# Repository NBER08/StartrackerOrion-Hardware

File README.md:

<h1 align="center">Orion Main</h1>

<p align="center" width="100%">
  
</p>

***

<p align="center">
  
&nbsp; &nbsp; &nbsp; &nbsp;
  
</p>

***

## SPECIFICATIONS

| Parameter | Value | 
| --- | --- |
| Dimensions | 86.06 × 71.93 mm |

***

## DIRECTORY STRUCTURE

    .
    ├─ Computations       # Misc calculations
    ├─ HTML               # HTML files for generated webpage
    ├─ Images             # Pictures and renders
    │
    ├─ kibot_resources    # External resources for KiBot
    │  ├─ colors          # Color theme for KiCad
    │  ├─ fonts           # Fonts used in the project
    │  ├─ scripts         # External scripts used with KiBot
    │  └─ templates       # Templates for KiBot generated reports
    │
    ├─ kibot_yaml         # KiBot YAML config files
    ├─ KiRI               # KiRI (PCB diff viewer) files
    │
    ├─ lib                # KiCad footprint and symbol libraries
    │  ├─ 3d_models       # Component 3D models
    │  ├─ lib_fp          # Footprint libraries
    │  └─ lib_sym         # Symbol libraries
    │
    ├─ Logos              # Logos
    │
    ├─ Manufacturing      # Assembly and fabrication documents
    │  ├─ Assembly        # Assembly documents (BoM, pos, notes)
    │  │
    │  └─ Fabrication     # Fabrication documents (ZIP, notes)
    │     ├─ Drill Tables # CSV drill tables
    │     └─ Gerbers      # Gerbers
    │
    ├─ Report             # Reports for ERC/DRC
    ├─ Schematic          # PDF of schematic
    ├─ Templates          # Title block templates
    ├─ Testing
    │  └─ Testpoints      # Testpoints tables      
    │
    └─ Variants           # Outputs for assembly variants

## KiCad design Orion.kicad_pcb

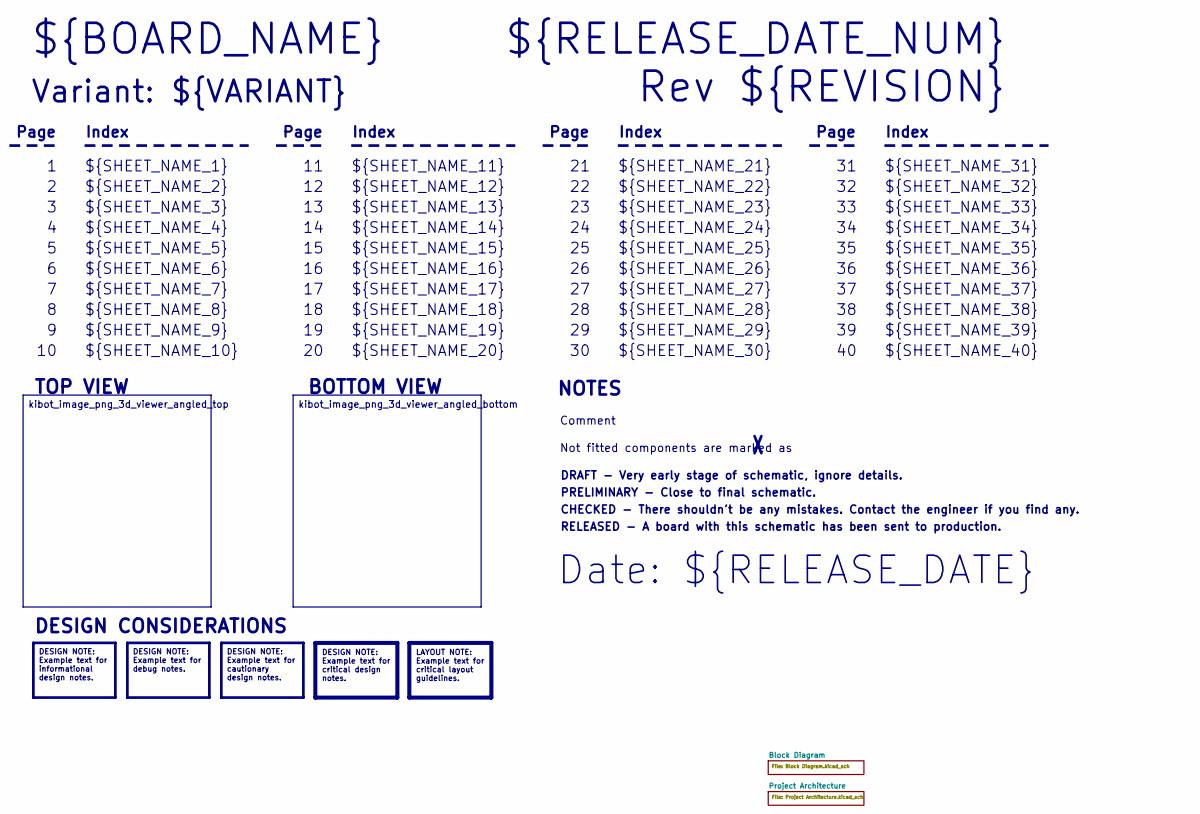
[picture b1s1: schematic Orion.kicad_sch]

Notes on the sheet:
Variant: ${VARIANT}
RELEASED - A board with this schematic has been sent to production.
${SHEET_NAME_24}
Index
Page
PRELIMINARY - Close to final schematic.
${SHEET_NAME_22}
DRAFT - Very early stage of schematic, ignore details.
${SHEET_NAME_12}
${SHEET_NAME_8}
${SHEET_NAME_2}
${SHEET_NAME_5}
${SHEET_NAME_20}
${SHEET_NAME_23}
${RELEASE_DATE_NUM}
${SHEET_NAME_35}
Not fitted components are marked as
${SHEET_NAME_11}
${SHEET_NAME_6}
${SHEET_NAME_37}
${SHEET_NAME_26}
${SHEET_NAME_36}
Rev ${REVISION}
${SHEET_NAME_15}
CHECKED - There shouldn't be any mistakes. Contact the engineer if you find any.
BOTTOM VIEW
${SHEET_NAME_14}
${SHEET_NAME_21}
${SHEET_NAME_17}
${SHEET_NAME_18}
Date: ${RELEASE_DATE}
${SHEET_NAME_7}
${SHEET_NAME_31}
${BOARD_NAME}
NOTES
${SHEET_NAME_40}
${SHEET_NAME_39}
${SHEET_NAME_32}
${SHEET_NAME_1}
${SHEET_NAME_9}

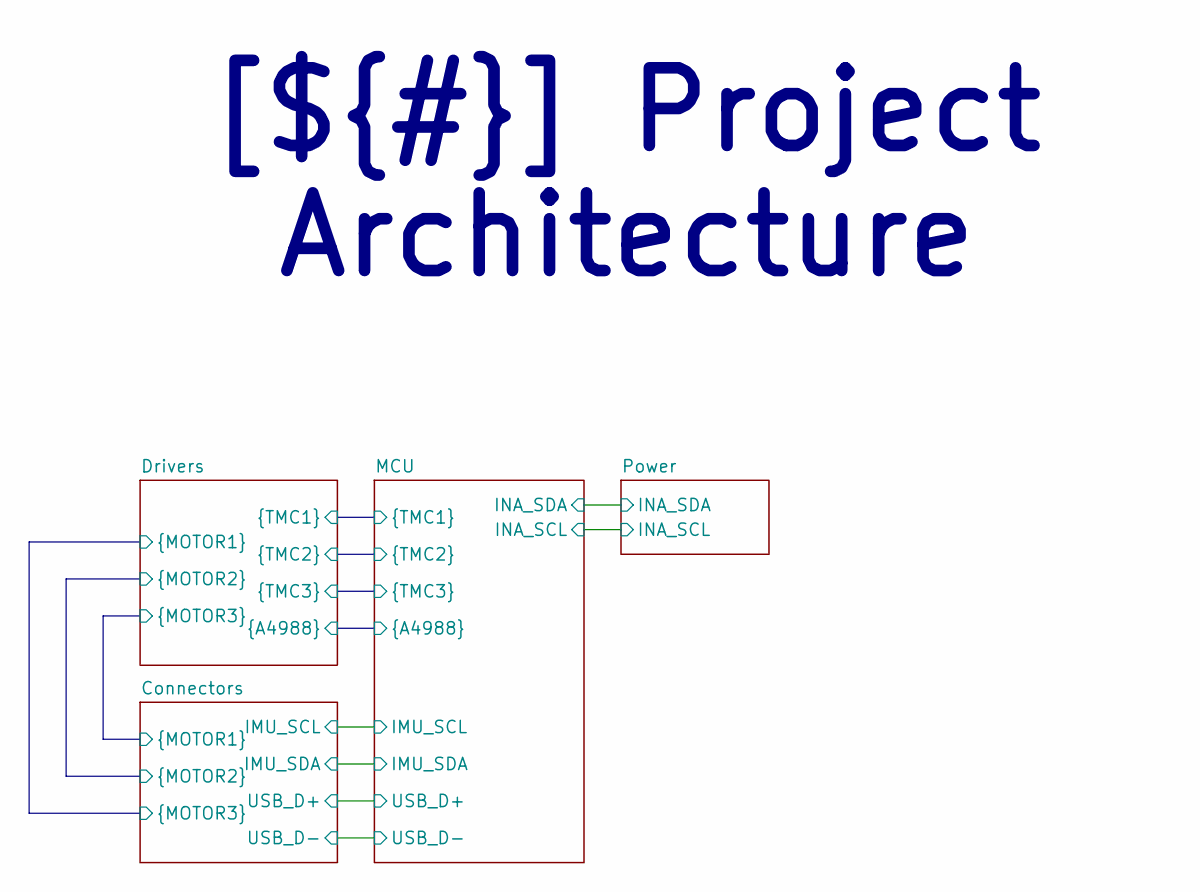
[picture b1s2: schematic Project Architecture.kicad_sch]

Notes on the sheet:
[${#}] ${TITLE}

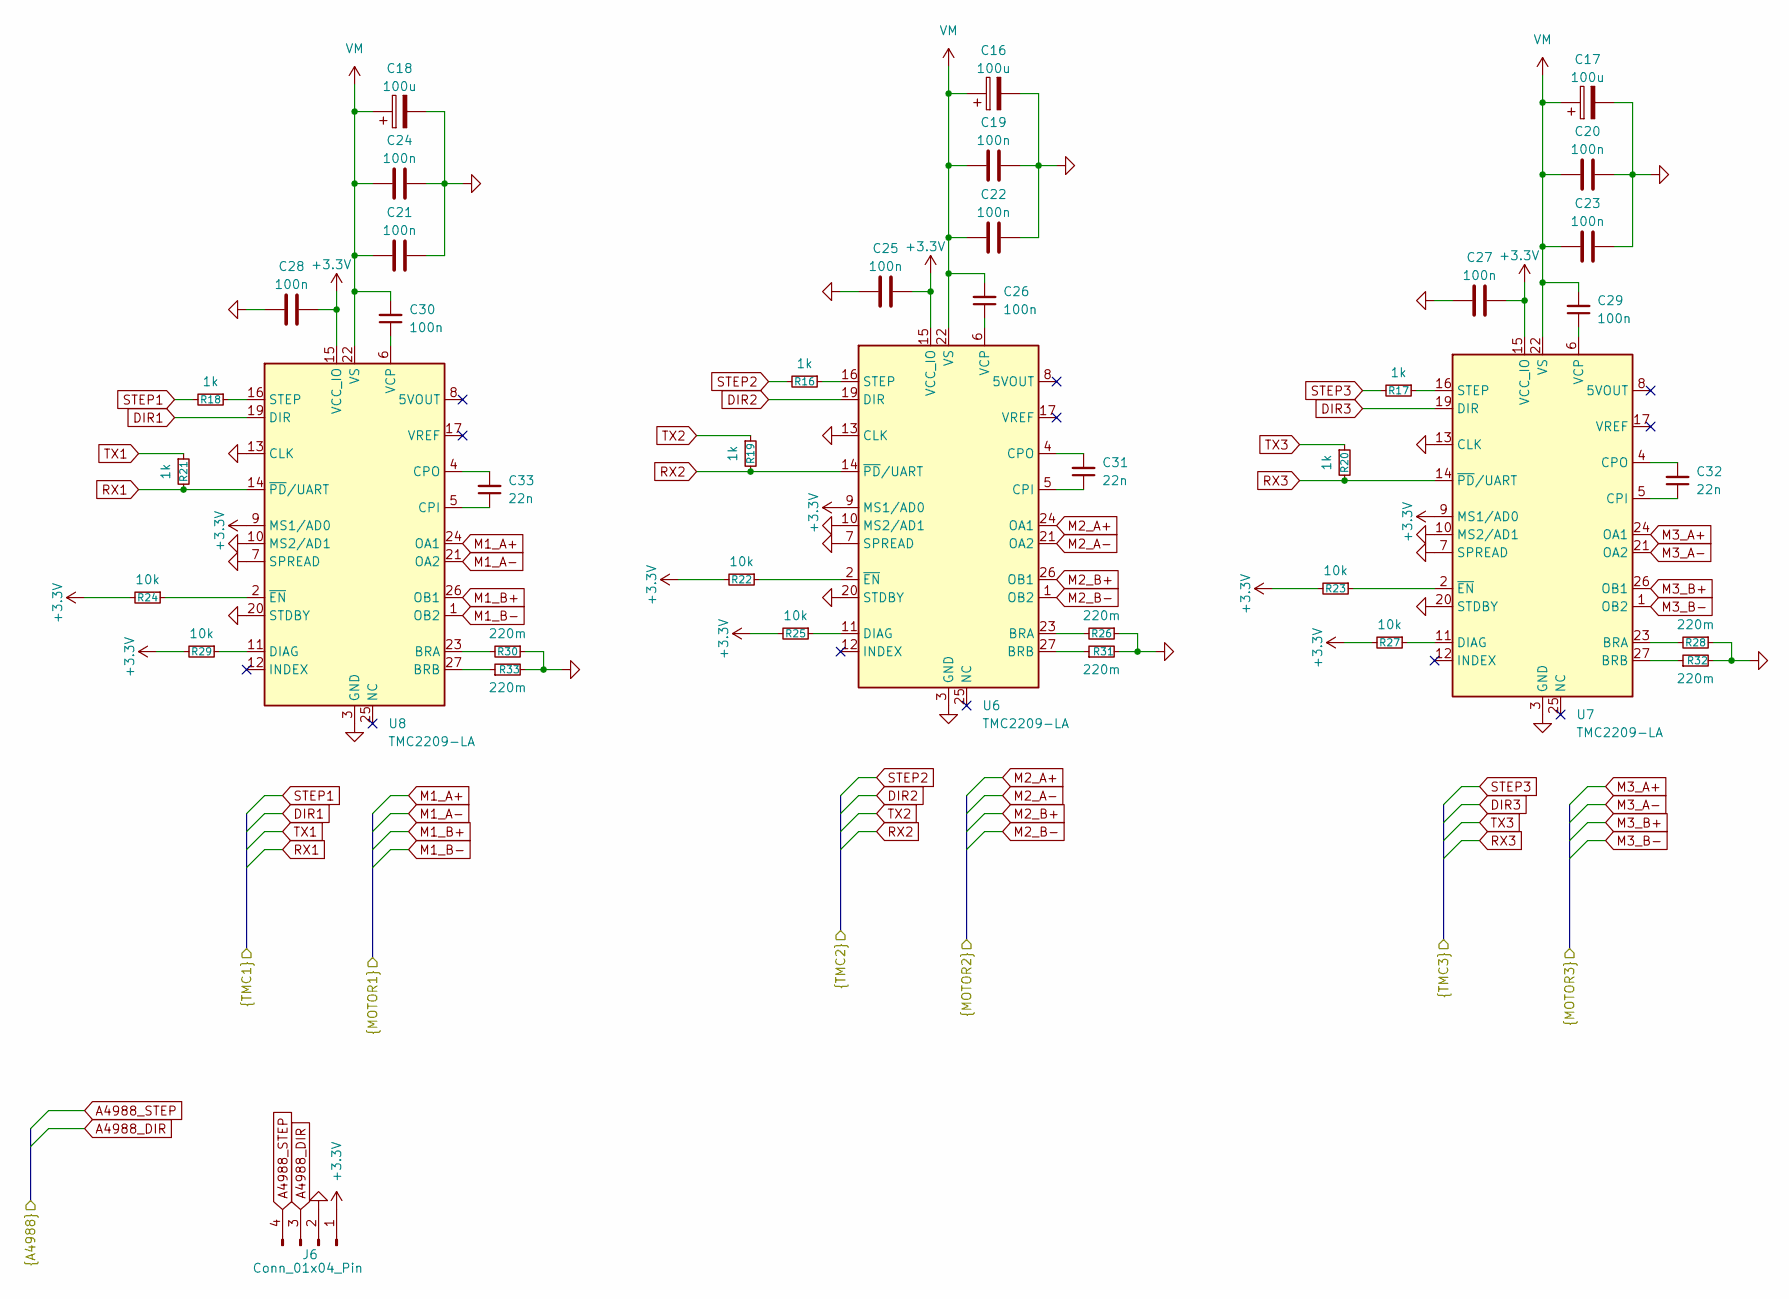
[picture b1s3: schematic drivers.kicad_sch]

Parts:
C16, C17, C18: 100u; CP_Radial_D5.0mm_P2.00mm
C19, C20, C21, C22, C23, C24, C25, C26, C27, C28, C29, C30: 100n; C_0603_1608Metric_Pad1.08x0.95mm_HandSolder
C31, C32, C33: 22n; C_0603_1608Metric_Pad1.08x0.95mm_HandSolder
J6: Conn_01x04_Pin; PinHeader_1x04_P2.54mm_Vertical
R16, R17, R18, R19, R20, R21: 1k; R_0603_1608Metric_Pad0.98x0.95mm_HandSolder
R22, R23, R24, R25, R27, R29: 10k; R_0603_1608Metric_Pad0.98x0.95mm_HandSolder
R26, R28, R30, R31, R32, R33: 220m; R_2512_6332Metric_Pad1.40x3.35mm_HandSolder
U6, U7, U8: TMC2209-LA; VQFN-28-1EP_5x5mm_P0.5mm_EP3.7x3.7mm

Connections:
+3.3V: C25.2, C27.2, C28.2, J6.1, R22.2, R23.2, R24.2, R25.2, R27.2, R29.2, U6.9 (MS1/AD0), U6.15 (VCC_IO), U7.9 (MS1/AD0), U7.15 (VCC_IO), U8.9 (MS1/AD0), U8.15 (VCC_IO); also elsewhere on the board
A4988_DIR: J6.3; also elsewhere on the board
A4988_STEP: J6.4; also elsewhere on the board
DIR1: U8.19 (DIR); also elsewhere on the board
DIR2: U6.19 (DIR); also elsewhere on the board
DIR3: U7.19 (DIR); also elsewhere on the board
GND: C16.2, C17.2, C18.2, C19.2, C20.2, C21.2, C22.2, C23.2, C24.2, C25.1, C27.1, C28.1, J6.2, R26.1, R28.1, R30.1, R31.2, R32.2, R33.2, U6.3 (GND), U6.7 (SPREAD), U6.10 (MS2/AD1), U6.13 (CLK), U6.18 (GND), U6.20 (STDBY), U6.29 (GND), U7.3 (GND), U7.7 (SPREAD), U7.10 (MS2/AD1), U7.13 (CLK), U7.18 (GND), U7.20 (STDBY), U7.29 (GND), U8.3 (GND), U8.7 (SPREAD), U8.10 (MS2/AD1), U8.13 (CLK), U8.18 (GND), U8.20 (STDBY), U8.29 (GND); also elsewhere on the board
M1_A+: U8.24 (OA1); also elsewhere on the board
M1_A-: U8.21 (OA2); also elsewhere on the board
M1_B+: U8.26 (OB1); also elsewhere on the board
M1_B-: U8.1 (OB2); also elsewhere on the board
M2_A+: U6.24 (OA1); also elsewhere on the board
M2_A-: U6.21 (OA2); also elsewhere on the board
M2_B+: U6.26 (OB1); also elsewhere on the board
M2_B-: U6.1 (OB2); also elsewhere on the board
M3_A+: U7.24 (OA1); also elsewhere on the board
M3_A-: U7.21 (OA2); also elsewhere on the board
M3_B+: U7.26 (OB1); also elsewhere on the board
M3_B-: U7.1 (OB2); also elsewhere on the board
unnamed: R26.2, U6.23 (BRA)
unnamed: R31.1, U6.27 (BRB)
unnamed: C31.1, U6.5 (CPI)
unnamed: C31.2, U6.4 (CPO)
unnamed: R25.1, U6.11 (DIAG)
unnamed: R16.1, U6.16 (STEP)
unnamed: C26.1, U6.6 (VCP)
unnamed: R22.1, U6.2 (~EN)
unnamed: R28.2, U7.23 (BRA)
unnamed: R32.1, U7.27 (BRB)
unnamed: C32.1, U7.5 (CPI)
unnamed: C32.2, U7.4 (CPO)
unnamed: R27.1, U7.11 (DIAG)
unnamed: R17.1, U7.16 (STEP)
unnamed: C29.1, U7.6 (VCP)
unnamed: R23.1, U7.2 (~EN)
unnamed: R30.2, U8.23 (BRA)
unnamed: R33.1, U8.27 (BRB)
unnamed: C33.1, U8.5 (CPI)
unnamed: C33.2, U8.4 (CPO)
unnamed: R29.1, U8.11 (DIAG)
unnamed: R18.1, U8.16 (STEP)
unnamed: C30.1, U8.6 (VCP)
unnamed: R24.1, U8.2 (~EN)
RX1: R21.2, U8.14 (~PD/UART); also elsewhere on the board
RX2: R19.2, U6.14 (~PD/UART); also elsewhere on the board
RX3: R20.2, U7.14 (~PD/UART); also elsewhere on the board
STEP1: R18.2; also elsewhere on the board
STEP2: R16.2; also elsewhere on the board
STEP3: R17.2; also elsewhere on the board
TX1: R21.1; also elsewhere on the board
TX2: R19.1; also elsewhere on the board
TX3: R20.1; also elsewhere on the board
VM: C16.1, C17.1, C18.1, C19.1, C20.1, C21.1, C22.1, C23.1, C24.1, C26.2, C29.2, C30.2, U6.22 (VS), U6.28 (VS), U7.22 (VS), U7.28 (VS), U8.22 (VS), U8.28 (VS); also elsewhere on the board

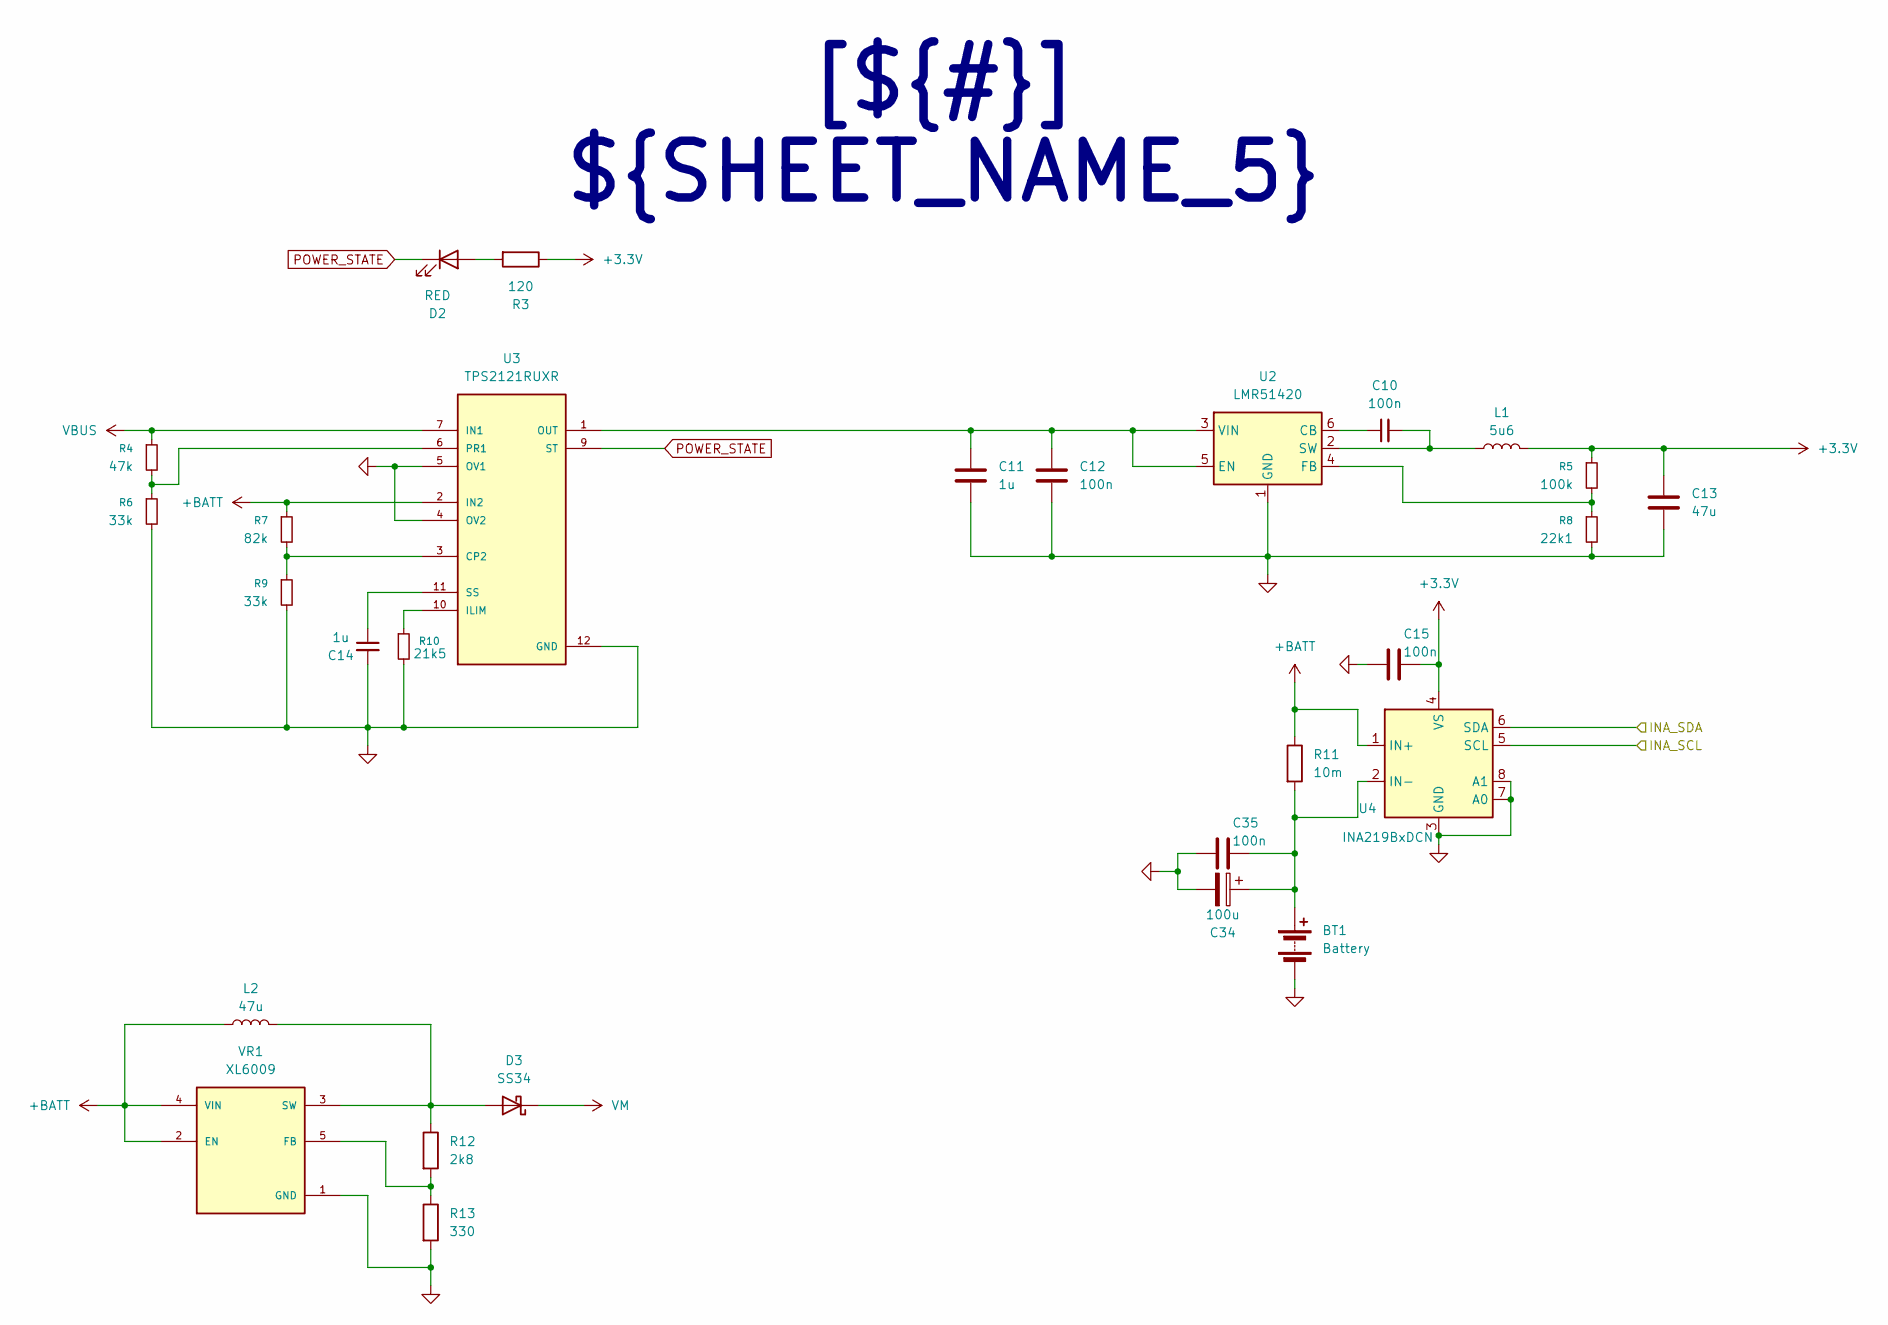
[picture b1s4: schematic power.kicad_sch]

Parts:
BT1: Battery; JST_XH_B2B-XH-A_1x02_P2.50mm_Vertical
C10, C12, C15, C35: 100n; C_0603_1608Metric_Pad1.08x0.95mm_HandSolder
C11, C14: 1u; C_0603_1608Metric_Pad1.08x0.95mm_HandSolder
C13: 47u; C_0603_1608Metric_Pad1.08x0.95mm_HandSolder
C34: 100u; CP_Radial_D5.0mm_P2.00mm
D2: RED; LED_0603_1608Metric_Pad1.05x0.95mm_HandSolder
D3: SS34; D_SMA_Handsoldering
L1: 5u6; WE-XHMI_4040
L2: 47u; L_Changjiang_FXL1365
R3: 120; R_0603_1608Metric_Pad0.98x0.95mm_HandSolder
R4: 47k; R_0603_1608Metric_Pad0.98x0.95mm_HandSolder
R5: 100k; R_0603_1608Metric_Pad0.98x0.95mm_HandSolder
R6, R9: 33k; R_0603_1608Metric_Pad0.98x0.95mm_HandSolder
R7: 82k; R_0603_1608Metric_Pad0.98x0.95mm_HandSolder
R8: 22k1; R_0603_1608Metric_Pad0.98x0.95mm_HandSolder
R10: 21k5; R_0603_1608Metric_Pad0.98x0.95mm_HandSolder
R11: 10m; R_0805_2012Metric_Pad1.20x1.40mm_HandSolder
R12: 2k8; R_0603_1608Metric_Pad0.98x0.95mm_HandSolder
R13: 330; R_0603_1608Metric_Pad0.98x0.95mm_HandSolder
U2: LMR51420; SOT-23-6_Handsoldering
U3: TPS2121RUXR; IC_TPS2121RUXR
U4: INA219BxDCN; SOT-23-8
VR1: XL6009; DPAK170P1435X465-6N; PARTREV 1.1

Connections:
+3.3V: C13.1, C15.2, L1.2, R3.1, R5.1, U4.4 (VS); also elsewhere on the board
+BATT: L2.1, R7.1, R11.1, U3.2 (IN2), U3.2_1 (IN2), U4.1 (IN+), VR1.2 (EN), VR1.4 (VIN); also elsewhere on the board
/Project Architecture/MCU/INA_SCL: U4.5 (SCL); also elsewhere on the board
/Project Architecture/MCU/INA_SDA: U4.6 (SDA); also elsewhere on the board
GND: BT1.2 (-), C11.2, C12.2, C13.2, C14.2, C15.1, C34.2, C35.1, R6.2, R8.2, R9.2, R10.2, R13.2, U2.1 (GND), U3.4 (OV2), U3.5 (OV1), U3.12 (GND), U4.3 (GND), U4.7 (A0), U4.8 (A1), VR1.1 (GND); also elsewhere on the board
unnamed: BT1.1 (+), C34.1, C35.2, R11.2, U4.2 (IN-)
unnamed: D2.2 (A), R3.2
unnamed: D3.2 (A), L2.2, R12.1, VR1.3 (SW), VR1.6 (SW)
unnamed: C10.1, U2.6 (CB)
unnamed: C11.1, C12.1, U2.3 (VIN), U2.5 (EN), U3.1 (OUT), U3.1_1 (OUT), U3.8 (OUT), U3.8_1 (OUT)
unnamed: R5.2, R8.1, U2.4 (FB)
unnamed: C10.2, L1.1, U2.2 (SW)
unnamed: R7.2, R9.1, U3.3 (CP2)
unnamed: R10.1, U3.10 (ILIM)
unnamed: R4.2, R6.1, U3.6 (PR1)
unnamed: C14.1, U3.11 (SS)
unnamed: R12.2, R13.1, VR1.5 (FB)
POWER_STATE: D2.1 (K), U3.9 (ST)
VBUS: R4.1, U3.7 (IN1), U3.7_1 (IN1); also elsewhere on the board
VM: D3.1 (K); also elsewhere on the board

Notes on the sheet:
[${#}] ${SHEET_NAME_5}

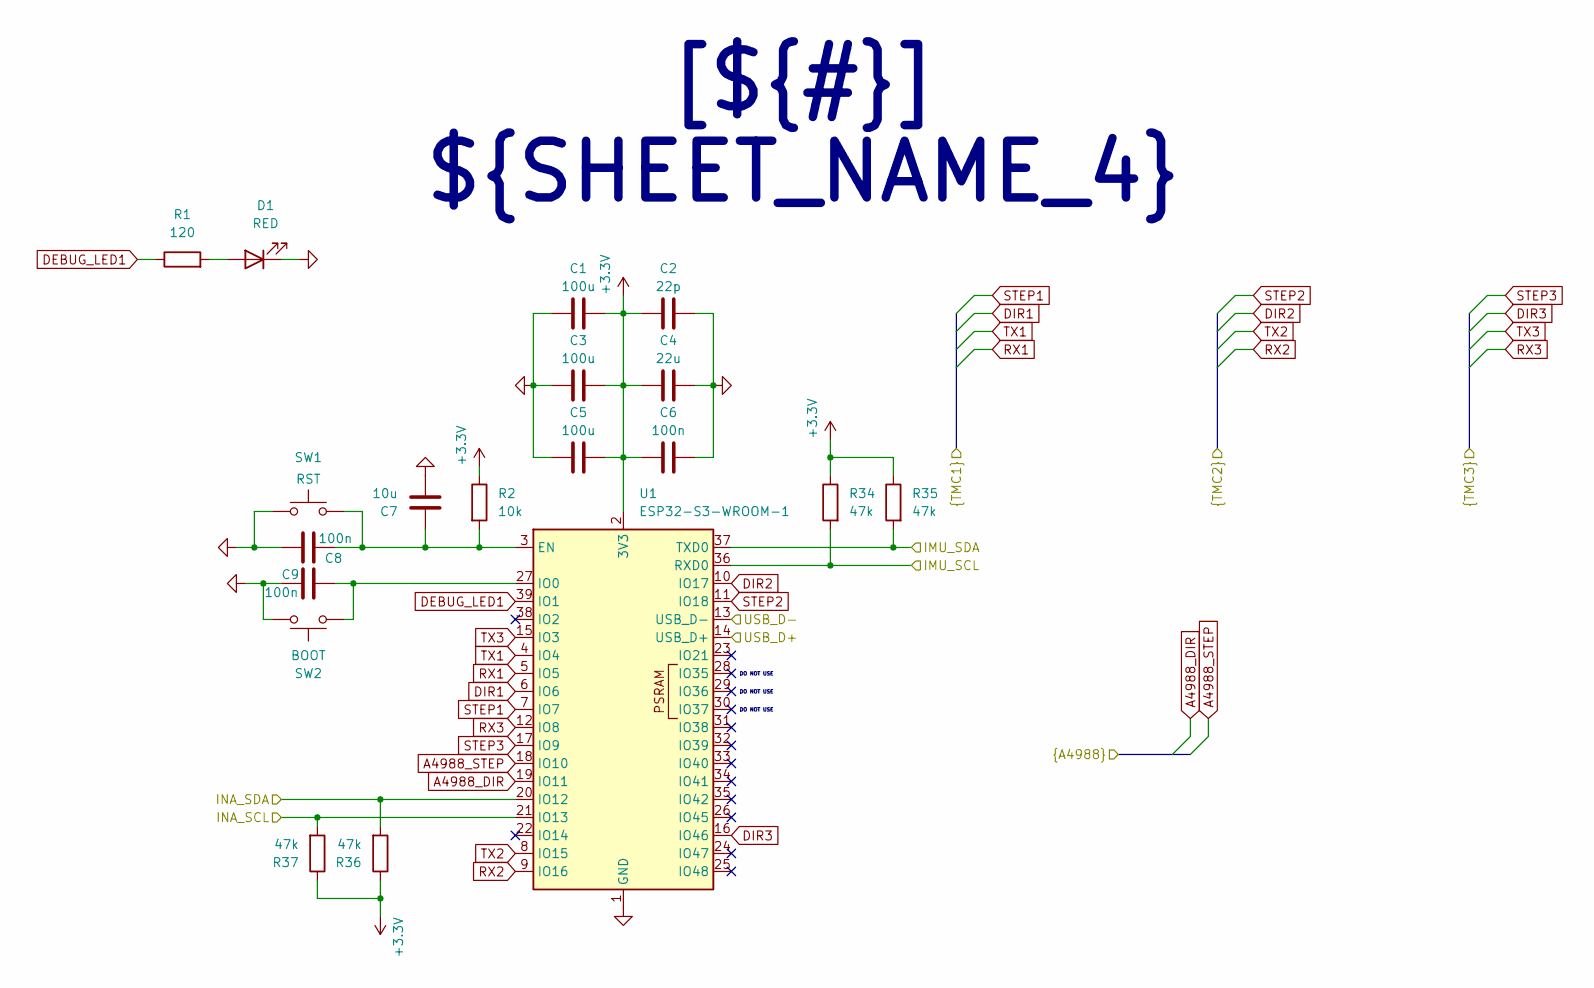
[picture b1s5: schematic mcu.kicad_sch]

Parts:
C1, C3, C5: 100u; C_1206_3216Metric_Pad1.33x1.80mm_HandSolder
C2: 22p; C_0603_1608Metric_Pad1.08x0.95mm_HandSolder
C4: 22u; C_0603_1608Metric_Pad1.08x0.95mm_HandSolder
C6, C8, C9: 100n; C_0603_1608Metric_Pad1.08x0.95mm_HandSolder
C7: 10u; C_0603_1608Metric_Pad1.08x0.95mm_HandSolder
D1: RED; LED_0603_1608Metric_Pad1.05x0.95mm_HandSolder
R1: 120; R_0603_1608Metric_Pad0.98x0.95mm_HandSolder
R2: 10k; R_0603_1608Metric_Pad0.98x0.95mm_HandSolder
R34, R35, R36, R37: 47k; R_0603_1608Metric_Pad0.98x0.95mm_HandSolder
SW1: RST; SW_SPST_PTS647_Sx38
SW2: BOOT; SW_SPST_PTS647_Sx38
U1: ESP32-S3-WROOM-1; ESP32-S3-WROOM-1_novias

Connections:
+3.3V: C1.2, C2.1, C3.2, C4.1, C5.2, C6.1, R2.1, R34.1, R35.1, R36.1, R37.1, U1.2 (3V3); also elsewhere on the board
/Project Architecture/Connectors/IMU_SCL: R34.2, U1.36 (RXD0); also elsewhere on the board
/Project Architecture/Connectors/IMU_SDA: R35.2, U1.37 (TXD0); also elsewhere on the board
/Project Architecture/Connectors/USB_D+: U1.14 (USB_D+); also elsewhere on the board
/Project Architecture/Connectors/USB_D-: U1.13 (USB_D-); also elsewhere on the board
/Project Architecture/MCU/INA_SCL: R37.2, U1.21 (IO13); also elsewhere on the board
/Project Architecture/MCU/INA_SDA: R36.2, U1.20 (IO12); also elsewhere on the board
A4988_DIR: U1.19 (IO11); also elsewhere on the board
A4988_STEP: U1.18 (IO10); also elsewhere on the board
DEBUG_LED1: R1.1, U1.39 (IO1)
DIR1: U1.6 (IO6); also elsewhere on the board
DIR2: U1.10 (IO17); also elsewhere on the board
DIR3: U1.16 (IO46); also elsewhere on the board
GND: C1.1, C2.2, C3.1, C4.2, C5.1, C6.2, C7.2, C8.1, C9.1, D1.1 (K), SW1.1, SW2.1, U1.1 (GND), U1.40 (GND), U1.41 (GND); also elsewhere on the board
unnamed: D1.2 (A), R1.2
unnamed: C7.1, C8.2, R2.2, SW1.2, U1.3 (EN)
unnamed: C9.2, SW2.2, U1.27 (IO0)
RX1: U1.5 (IO5); also elsewhere on the board
RX2: U1.9 (IO16); also elsewhere on the board
RX3: U1.12 (IO8); also elsewhere on the board
STEP1: U1.7 (IO7); also elsewhere on the board
STEP2: U1.11 (IO18); also elsewhere on the board
STEP3: U1.17 (IO9); also elsewhere on the board
TX1: U1.4 (IO4); also elsewhere on the board
TX2: U1.8 (IO15); also elsewhere on the board
TX3: U1.15 (IO3); also elsewhere on the board

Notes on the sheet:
DO NOT USE
[${#}] ${SHEET_NAME_4}

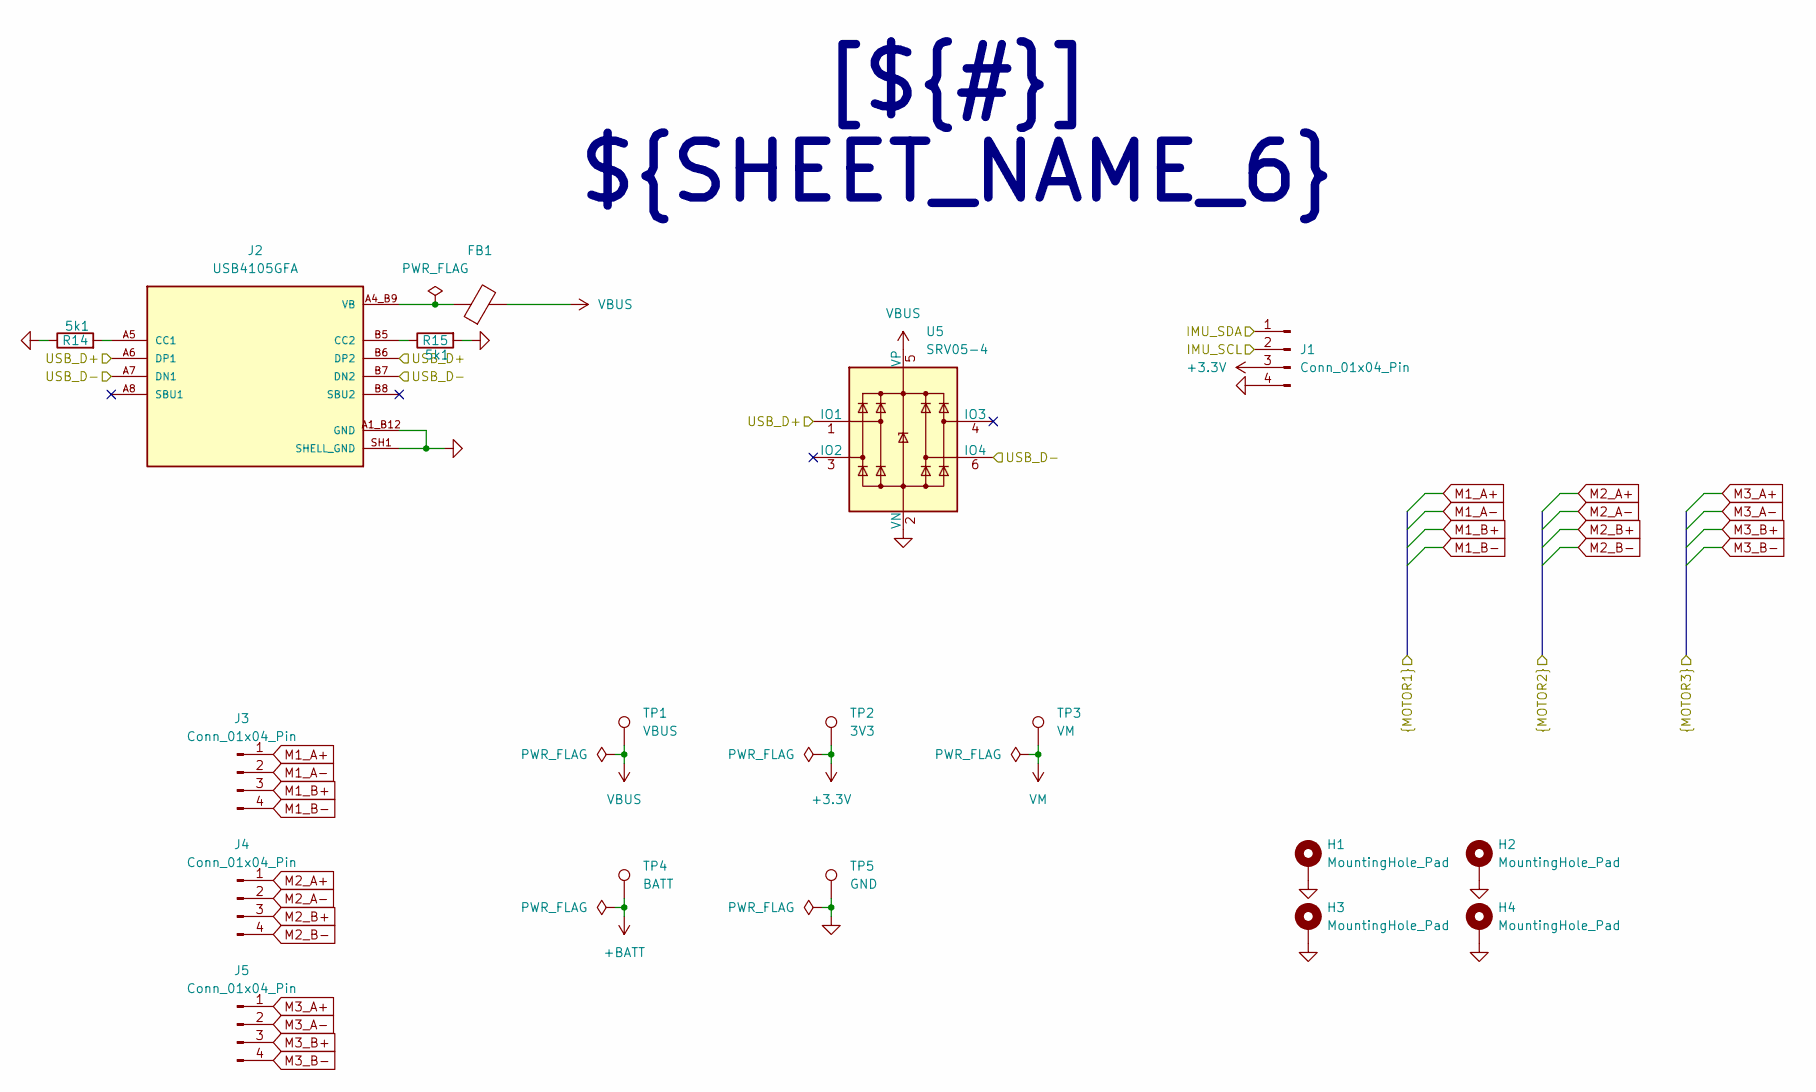
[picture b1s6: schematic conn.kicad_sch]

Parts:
FB1: LI0603G121R-10; L_0603_1608Metric_Pad1.05x0.95mm_HandSolder
H1, H2, H3, H4: MountingHole_Pad; MountingHole_3.2mm_M3_DIN965_Pad
J1: Conn_01x04_Pin; PinHeader_1x04_P2.54mm_Vertical
J2: USB4105GFA; GCT_USB4105GFA; PARTREV B3
J3, J4, J5: Conn_01x04_Pin; JST_XH_B4B-XH-A_1x04_P2.50mm_Vertical
R14, R15: 5k1; R_0603_1608Metric_Pad0.98x0.95mm_HandSolder
TP1: VBUS; TestPoint_Pad_D1.5mm
TP2: 3V3; TestPoint_Pad_D1.5mm
TP3: VM; TestPoint_Pad_D1.5mm
TP4: BATT; TestPoint_Pad_D1.5mm
TP5: GND; TestPoint_Pad_D1.5mm
U5: SRV05-4; SOT-23-6_Handsoldering

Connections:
+3.3V: J1.3, TP2.1 (1_1); also elsewhere on the board
+BATT: TP4.1 (1_1); also elsewhere on the board
/Project Architecture/Connectors/IMU_SCL: J1.2; also elsewhere on the board
/Project Architecture/Connectors/IMU_SDA: J1.1; also elsewhere on the board
/Project Architecture/Connectors/USB_D+: J2.A6 (DP1), J2.B6 (DP2), U5.1 (IO1); also elsewhere on the board
/Project Architecture/Connectors/USB_D-: J2.A7 (DN1), J2.B7 (DN2), U5.6 (IO4); also elsewhere on the board
GND: H1.1 (1_1), H2.1 (1_1), H3.1 (1_1), H4.1 (1_1), J1.4, J2.A1_B12 (GND), J2.B1_A12 (GND), J2.SH1 (SHELL_GND), J2.SH2 (SHELL_GND), J2.SH3 (SHELL_GND), J2.SH4 (SHELL_GND), R14.1, R15.2, TP5.1 (1_1), U5.2 (VN); also elsewhere on the board
M1_A+: J3.1; also elsewhere on the board
M1_A-: J3.2; also elsewhere on the board
M1_B+: J3.3; also elsewhere on the board
M1_B-: J3.4; also elsewhere on the board
M2_A+: J4.1; also elsewhere on the board
M2_A-: J4.2; also elsewhere on the board
M2_B+: J4.3; also elsewhere on the board
M2_B-: J4.4; also elsewhere on the board
M3_A+: J5.1; also elsewhere on the board
M3_A-: J5.2; also elsewhere on the board
M3_B+: J5.3; also elsewhere on the board
M3_B-: J5.4; also elsewhere on the board
unnamed: J2.A5 (CC1), R14.2
unnamed: J2.B5 (CC2), R15.1
VB: FB1.1, J2.A4_B9 (VB), J2.B4_A9 (VB)
VBUS: FB1.2, TP1.1 (1_1), U5.5 (VP); also elsewhere on the board
VM: TP3.1 (1_1); also elsewhere on the board

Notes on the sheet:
[${#}] ${SHEET_NAME_6}

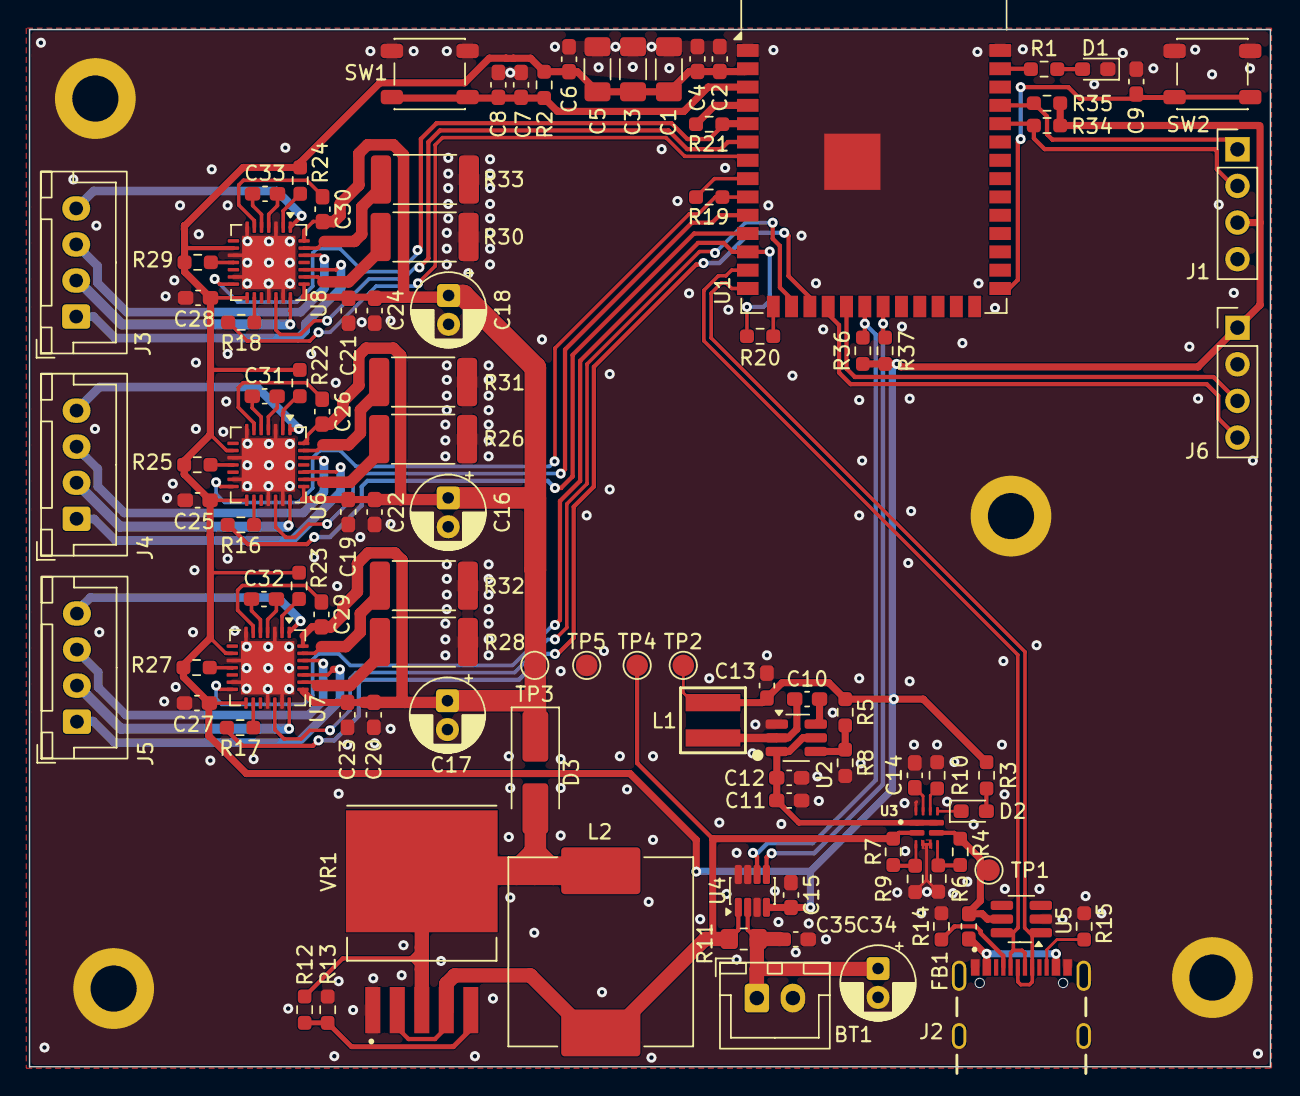
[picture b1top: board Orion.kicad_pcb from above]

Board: 2 copper layers, 86.1 x 71.9 mm, 105 parts (0 on the bottom side), 81 nets.

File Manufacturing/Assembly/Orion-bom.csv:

Row,Quantity Per PCB,References,Value,Datasheet,Footprint,Description,Manufacturer,Manufacturer Part Number,Supplier Part Number
1,1,BT1,Battery,,JST_XH_B2B-XH-A_1x02_P2.50mm_Vertical,Multiple-cell battery,,,
2,1,C2,22p,,C_0603_1608Metric_Pad1.08x0.95mm_HandSolder,Unpolarized capacitor,,,
3,3,C31 C32 C33,22n,,C_0603_1608Metric_Pad1.08x0.95mm_HandSolder,50V,,,
4,19,C6 C8 C9 C10 C12 C15 C19 C20 C21 C22 C23 C24 C25 C26 C27 C28 C29 C30 C35,100n,,C_0603_1608Metric_Pad1.08x0.95mm_HandSolder,"Unpolarized capacitor Unpolarized capacitor, small symbol 16V",,,
5,2,C11 C14,1u,,C_0603_1608Metric_Pad1.08x0.95mm_HandSolder,"Unpolarized capacitor Unpolarized capacitor, small symbol",,,
6,1,C7,10u,,C_0603_1608Metric_Pad1.08x0.95mm_HandSolder,Unpolarized capacitor,,,
7,1,C4,22u,,C_0603_1608Metric_Pad1.08x0.95mm_HandSolder,Unpolarized capacitor,,,
8,2,C13 L2,47u,,C_0603_1608Metric_Pad1.08x0.95mm_HandSolder,Unpolarized capacitor Inductor,,,
9,7,C1 C3 C5 C16 C17 C18 C34,100u,,C_1206_3216Metric_Pad1.33x1.80mm_HandSolder,Unpolarized capacitor low ESR,,,
10,2,D1 D2,RED,,LED_0603_1608Metric_Pad1.05x0.95mm_HandSolder,Light emitting diode,,,
11,1,D3,SS34,https://www.vishay.com/docs/88751/ss32.pdf,D_SMA_Handsoldering,"40V 3A Schottky Diode, SMA",,,
12,1,FB1,LI0603G121R-10,,L_0603_1608Metric_Pad1.05x0.95mm_HandSolder,Ferrite bead,,,
13,5,J1 J3 J4 J5 J6,Conn_01x04_Pin,,PinHeader_1x04_P2.54mm_Vertical,"Generic connector, single row, 01x04, script generated",,,
14,1,J2,USB4105GFA,,GCT_USB4105GFA,"USB-C (USB TYPE-C) USB 2.0 Receptacle Connector 24 (16+8 Dummy) Position Surface Mount, Right Angle; Through Hole",Global Connector Technology,,
15,1,L1,5u6,,WE-XHMI_4040,Inductor,,,
16,1,R11,10m,,R_0805_2012Metric_Pad1.20x1.40mm_HandSolder,Resistor,,,
17,6,R26 R28 R30 R31 R32 R33,220m,,R_2512_6332Metric_Pad1.40x3.35mm_HandSolder,"Resistor, small symbol",,,
18,2,R1 R3,120,,R_0603_1608Metric_Pad0.98x0.95mm_HandSolder,Resistor,,,
19,1,R13,330,,R_0603_1608Metric_Pad0.98x0.95mm_HandSolder,Resistor,,,
20,6,R16 R17 R18 R19 R20 R21,1k,,R_0603_1608Metric_Pad0.98x0.95mm_HandSolder,"Resistor, small symbol",,,
21,1,R12,2k8,,R_0603_1608Metric_Pad0.98x0.95mm_HandSolder,Resistor,,,
22,2,R14 R15,5k1,,R_0603_1608Metric_Pad0.98x0.95mm_HandSolder,Resistor,,,
23,7,R2 R22 R23 R24 R25 R27 R29,10k,,R_0603_1608Metric_Pad0.98x0.95mm_HandSolder,"Resistor Resistor, small symbol",,,
24,1,R10,21k5,,R_0603_1608Metric_Pad0.98x0.95mm_HandSolder,"Resistor, small symbol",,,
25,1,R8,22k1,,R_0603_1608Metric_Pad0.98x0.95mm_HandSolder,"Resistor, small symbol",,,
26,2,R6 R9,33k,,R_0603_1608Metric_Pad0.98x0.95mm_HandSolder,"Resistor, small symbol",,,
27,5,R4 R34 R35 R36 R37,47k,,R_0603_1608Metric_Pad0.98x0.95mm_HandSolder,"Resistor, small symbol",,,
28,1,R7,82k,,R_0603_1608Metric_Pad0.98x0.95mm_HandSolder,"Resistor, small symbol",,,
29,1,R5,100k,,R_0603_1608Metric_Pad0.98x0.95mm_HandSolder,"Resistor, small symbol",,,
30,1,SW2,BOOT,,SW_SPST_PTS647_Sx38,"Push button switch, generic, two pins",,,
31,1,SW1,RST,,SW_SPST_PTS647_Sx38,"Push button switch, generic, two pins",,,
32,1,U1,ESP32-S3-WROOM-1,https://www.espressif.com/sites/default/files/documentation/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,ESP32-S3-WROOM-1_novias,"RF Module, ESP32-S3 SoC, Wi-Fi 802.11b/g/n, Bluetooth, BLE, 32-bit, 3.3V, onboard antenna, SMD",,,
33,1,U4,INA219BxDCN,http://www.ti.com/lit/ds/symlink/ina219.pdf,SOT-23-8,"Zero-Drift, HighAccuracy, Bidirectional Current/Power Monitor (0-26V) With I2C Interface, SOT-23-8",,,
34,1,U2,LMR51420,https://www.ti.com/lit/ds/symlink/lmr51430.pdf,SOT-23-6_Handsoldering,"4.5-V to 36-V, 3-A synchronous buck converter with 40-µA IQ, SOT-23-6",,,
35,1,U5,SRV05-4,http://www.onsemi.com/pub/Collateral/SRV05-4-D.PDF,SOT-23-6_Handsoldering,"ESD Protection Diodes with Low Clamping Voltage, SOT-23-6",,,
36,3,U6 U7 U8,TMC2209-LA,https://www.analog.com/media/en/technical-documentation/data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,VQFN-28-1EP_5x5mm_P0.5mm_EP3.7x3.7mm,"2-phase stepper motor driver, 256 µSteps, 2.8A peak, 2.0A RMS, VS = 4.75..29V, STEP/DIR and UART interface, VQFN-28",,,
37,1,U3,TPS2121RUXR,,IC_TPS2121RUXR,"2.7-V to 22-V, 56-mΩ, 4.5-A, power mux with seamless switchover",TEXAS INSTRUMENTS,,
38,1,VR1,XL6009,,DPAK170P1435X465-6N,"The XL6009 regulator is a wide input range, current mode, DC/DC converter which is capable of generating either positive or negative output voltages.",XLSEMI,,
